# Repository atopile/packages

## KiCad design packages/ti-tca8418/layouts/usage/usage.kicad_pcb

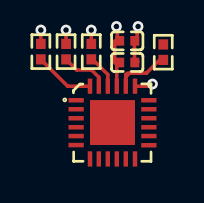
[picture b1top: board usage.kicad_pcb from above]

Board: 2 copper layers, 7 parts (0 on the bottom side), 6 nets.

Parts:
C1: 1±10.0%F; C0402
C2: {7.999..1.2}F; C0402
R1, R2, R3, R4: 10000±1.0%Ω; R0402
U1: WQFN-24_L4.0-W4.0-P0.50-TL-EP2.5

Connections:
SCL: R1.1, U1.23
SDA: R2.1, U1.22
hv: C1.1, C2.1, R1.2, R2.2, R4.2, U1.21
lv: C1.2, C2.2, R3.2, U1.19
nINT: R3.1, U1.24
nRESET: R4.1, U1.20

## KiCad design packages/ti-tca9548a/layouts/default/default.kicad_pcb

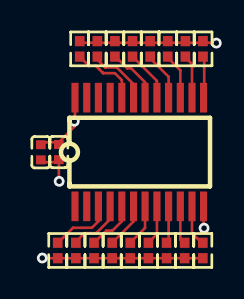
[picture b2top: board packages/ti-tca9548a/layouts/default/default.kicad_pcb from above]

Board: 2 copper layers, 20 parts (0 on the bottom side), 19 nets.

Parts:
C1, C2: [capacitance: unknown]; C0402
R1, R2, R3, R4, R5, R6, R7, R8, R9, R10, R11, R12, R13, R14, R15, R16, R17: [resistance: unknown]; R0402
U1: TSSOP-24_L7.8-W4.4-P0.65-LS6.4-BL

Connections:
hv: C1.1, C2.1, R1.2, R2.2, R3.2, R4.2, R5.2, R6.2, R7.2, R8.2, R9.2, R10.2, R11.2, R12.2, R13.2, R14.2, R15.2, R16.2, R17.2, U1.24
i2cs[0]-SCL: R2.1, U1.5
i2cs[0]-SDA: R10.1, U1.4
i2cs[1]-SCL: R3.1, U1.7
i2cs[1]-SDA: R11.1, U1.6
i2cs[2]-SCL: R4.1, U1.9
i2cs[2]-SDA: R12.1, U1.8
i2cs[3]-SCL: R5.1, U1.11
i2cs[3]-SDA: R13.1, U1.10
i2cs[4]-SCL: R6.1, U1.14
i2cs[4]-SDA: R14.1, U1.13
i2cs[5]-SCL: R7.1, U1.16
i2cs[5]-SDA: R15.1, U1.15
i2cs[6]-SCL: R8.1, U1.18
i2cs[6]-SDA: R16.1, U1.17
i2cs[7]-SCL: R9.1, U1.20
i2cs[7]-SDA: R17.1, U1.19
lv: C1.2, C2.2, U1.1, U1.2, U1.12, U1.21
nRESET: R1.1, U1.3

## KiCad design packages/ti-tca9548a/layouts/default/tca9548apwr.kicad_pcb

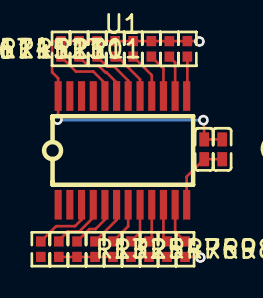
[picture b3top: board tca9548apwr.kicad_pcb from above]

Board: 2 copper layers, 20 parts (0 on the bottom side), 19 nets.

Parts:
C1: 100nF ±10% 16V X7R; C0402
C2: 2.2µF ±20% 6.3V X5R; C0402
R1: 10kΩ ±1% 62.5mW; R0402
R2, R3, R4, R5, R6, R7, R8, R9, R10, R11, R12, R13, R14, R15, R16, R17: 2kΩ ±1% 62.5mW; R0402
U1: TSSOP-24_L7.8-W4.4-P0.65-LS6.4-BL

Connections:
RESET: R1.1, U1.3
SC0: R2.1, U1.5
SC1: R4.1, U1.7
SC2: R6.1, U1.9
SC3: R8.1, U1.11
SC4: R10.1, U1.14
SC5: R12.1, U1.16
SC6: R14.1, U1.18
SC7: R16.1, U1.20
SD0: R3.1, U1.4
SD1: R5.1, U1.6
SD2: R7.1, U1.8
SD3: R9.1, U1.10
SD4: R11.1, U1.13
SD5: R13.1, U1.15
SD6: R15.1, U1.17
SD7: R17.1, U1.19
gnd: C1.2, C2.2, U1.12
hv: C1.1, C2.1, R1.2, R2.2, R3.2, R4.2, R5.2, R6.2, R7.2, R8.2, R9.2, R10.2, R11.2, R12.2, R13.2, R14.2, R15.2, R16.2, R17.2, U1.24

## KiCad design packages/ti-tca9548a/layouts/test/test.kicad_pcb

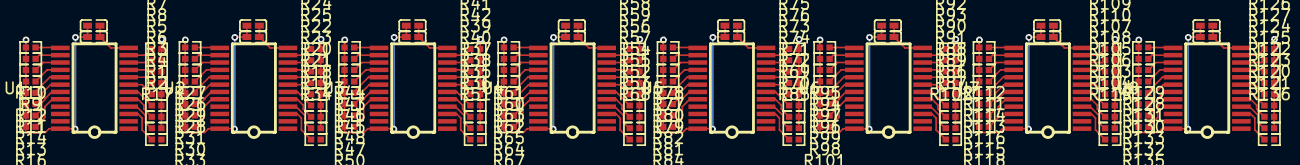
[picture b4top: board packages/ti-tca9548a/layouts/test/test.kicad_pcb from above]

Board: 2 copper layers, 160 parts (0 on the bottom side), 140 nets.

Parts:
C1, C3, C5, C7, C9, C11, C13, C15: 100nF ±10% 16V X7R; C0402
C2, C4, C6, C8, C10, C12, C14, C16: 2.2µF ±20% 6.3V X5R; C0402
R1, R2, R3, R4, R5, R6, R7, R8, R9, R10, R11, R12, R13, R14, R15, R16, R18, R19, R20, R21, R22, R23, R24, R25, R26, R27, R28, R29, R30, R31, R32, R33, R35, R36, R37, R38, R39, R40, R41, R42, R43, R44, R45, R46, R47, R48, R49, R50, R52, R53, R54, R55, R56, R57, R58, R59, R60, R61, R62, R63, R64, R65, R66, R67, R69, R70, R71, R72, R73, R74, R75, R76, R77, R78, R79, R80, R81, R82, R83, R84, R86, R87, R88, R89, R90, R91, R92, R93, R94, R95, R96, R97, R98, R99, R100, R101, R103, R104, R105, R106, R107, R108, R109, R110, R111, R112, R113, R114, R115, R116, R117, R118, R120, R121, R122, R123, R124, R125, R126, R127, R128, R129, R130, R131, R132, R133, R134, R135: 2kΩ ±1% 62.5mW; R0402
R17, R34, R51, R68, R85, R102, R119, R136: 10kΩ ±1% 62.5mW; R0402
U1, U2, U3, U4, U5, U6, U7, U8: TSSOP-24_L7.8-W4.4-P0.65-LS6.4-BL

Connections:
SCL: U1.22, U2.22, U3.22, U4.22, U5.22, U6.22, U7.22, U8.22
SDA: U1.23, U2.23, U3.23, U4.23, U5.23, U6.23, U7.23, U8.23
gnd: C1.2, C2.2, C3.2, C4.2, C5.2, C6.2, C7.2, C8.2, C9.2, C10.2, C11.2, C12.2, C13.2, C14.2, C15.2, C16.2, U1.1, U1.2, U1.12, U1.21, U2.2, U2.12, U2.21, U3.1, U3.12, U3.21, U4.12, U4.21, U5.1, U5.2, U5.12, U6.2, U6.12, U7.1, U7.12, U8.12
hv: C1.1, C2.1, C3.1, C4.1, C5.1, C6.1, C7.1, C8.1, C9.1, C10.1, C11.1, C12.1, C13.1, C14.1, C15.1, C16.1, R1.2, R2.2, R3.2, R4.2, R5.2, R6.2, R7.2, R8.2, R9.2, R10.2, R11.2, R12.2, R13.2, R14.2, R15.2, R16.2, R17.2, R18.2, R19.2, R20.2, R21.2, R22.2, R23.2, R24.2, R25.2, R26.2, R27.2, R28.2, R29.2, R30.2, R31.2, R32.2, R33.2, R34.2, R35.2, R36.2, R37.2, R38.2, R39.2, R40.2, R41.2, R42.2, R43.2, R44.2, R45.2, R46.2, R47.2, R48.2, R49.2, R50.2, R51.2, R52.2, R53.2, R54.2, R55.2, R56.2, R57.2, R58.2, R59.2, R60.2, R61.2, R62.2, R63.2, R64.2, R65.2, R66.2, R67.2, R68.2, R69.2, R70.2, R71.2, R72.2, R73.2, R74.2, R75.2, R76.2, R77.2, R78.2, R79.2, R80.2, R81.2, R82.2, R83.2, R84.2, R85.2, R86.2, R87.2, R88.2, R89.2, R90.2, R91.2, R92.2, R93.2, R94.2, R95.2, R96.2, R97.2, R98.2, R99.2, R100.2, R101.2, R102.2, R103.2, R104.2, R105.2, R106.2, R107.2, R108.2, R109.2, R110.2, R111.2, R112.2, R113.2, R114.2, R115.2, R116.2, R117.2, R118.2, R119.2, R120.2, R121.2, R122.2, R123.2, R124.2, R125.2, R126.2, R127.2, R128.2, R129.2, R130.2, R131.2, R132.2, R133.2, R134.2, R135.2, R136.2, U1.24, U2.1, U2.24, U3.2, U3.24, U4.1, U4.2, U4.24, U5.21, U5.24, U6.1, U6.21, U6.24, U7.2, U7.21, U7.24, U8.1, U8.2, U8.21, U8.24
muxes[0]-RESET: R17.1, U1.3
muxes[0]-SC0: R1.1, U1.5
muxes[0]-SC1: R3.1, U1.7
muxes[0]-SC2: R5.1, U1.9
muxes[0]-SC3: R7.1, U1.11
muxes[0]-SC4: R9.1, U1.14
muxes[0]-SC5: R11.1, U1.16
muxes[0]-SC6: R13.1, U1.18
muxes[0]-SC7: R15.1, U1.20
muxes[0]-SD0: R2.1, U1.4
muxes[0]-SD1: R4.1, U1.6
muxes[0]-SD2: R6.1, U1.8
muxes[0]-SD3: R8.1, U1.10
muxes[0]-SD4: R10.1, U1.13
muxes[0]-SD5: R12.1, U1.15
muxes[0]-SD6: R14.1, U1.17
muxes[0]-SD7: R16.1, U1.19
muxes[1]-RESET: R34.1, U2.3
muxes[1]-SC0: R18.1, U2.5
muxes[1]-SC1: R20.1, U2.7
muxes[1]-SC2: R22.1, U2.9
muxes[1]-SC3: R24.1, U2.11
muxes[1]-SC4: R26.1, U2.14
muxes[1]-SC5: R28.1, U2.16
muxes[1]-SC6: R30.1, U2.18
muxes[1]-SC7: R32.1, U2.20
muxes[1]-SD0: R19.1, U2.4
muxes[1]-SD1: R21.1, U2.6
muxes[1]-SD2: R23.1, U2.8
muxes[1]-SD3: R25.1, U2.10
muxes[1]-SD4: R27.1, U2.13
muxes[1]-SD5: R29.1, U2.15
muxes[1]-SD6: R31.1, U2.17
muxes[1]-SD7: R33.1, U2.19
muxes[2]-RESET: R51.1, U3.3
muxes[2]-SC0: R35.1, U3.5
muxes[2]-SC1: R37.1, U3.7
muxes[2]-SC2: R39.1, U3.9
muxes[2]-SC3: R41.1, U3.11
muxes[2]-SC4: R43.1, U3.14
muxes[2]-SC5: R45.1, U3.16
muxes[2]-SC6: R47.1, U3.18
muxes[2]-SC7: R49.1, U3.20
muxes[2]-SD0: R36.1, U3.4
muxes[2]-SD1: R38.1, U3.6
muxes[2]-SD2: R40.1, U3.8
muxes[2]-SD3: R42.1, U3.10
muxes[2]-SD4: R44.1, U3.13
muxes[2]-SD5: R46.1, U3.15
muxes[2]-SD6: R48.1, U3.17
muxes[2]-SD7: R50.1, U3.19
muxes[3]-RESET: R68.1, U4.3
muxes[3]-SC0: R52.1, U4.5
muxes[3]-SC1: R54.1, U4.7
muxes[3]-SC2: R56.1, U4.9
muxes[3]-SC3: R58.1, U4.11
muxes[3]-SC4: R60.1, U4.14
muxes[3]-SC5: R62.1, U4.16
muxes[3]-SC6: R64.1, U4.18
muxes[3]-SC7: R66.1, U4.20
muxes[3]-SD0: R53.1, U4.4
muxes[3]-SD1: R55.1, U4.6
muxes[3]-SD2: R57.1, U4.8
muxes[3]-SD3: R59.1, U4.10
muxes[3]-SD4: R61.1, U4.13
muxes[3]-SD5: R63.1, U4.15
muxes[3]-SD6: R65.1, U4.17
muxes[3]-SD7: R67.1, U4.19
muxes[4]-RESET: R85.1, U5.3
muxes[4]-SC0: R69.1, U5.5
muxes[4]-SC1: R71.1, U5.7
muxes[4]-SC2: R73.1, U5.9
muxes[4]-SC3: R75.1, U5.11
muxes[4]-SC4: R77.1, U5.14
muxes[4]-SC5: R79.1, U5.16
muxes[4]-SC6: R81.1, U5.18
muxes[4]-SC7: R83.1, U5.20
muxes[4]-SD0: R70.1, U5.4
muxes[4]-SD1: R72.1, U5.6
muxes[4]-SD2: R74.1, U5.8
muxes[4]-SD3: R76.1, U5.10
muxes[4]-SD4: R78.1, U5.13
muxes[4]-SD5: R80.1, U5.15
muxes[4]-SD6: R82.1, U5.17
muxes[4]-SD7: R84.1, U5.19
muxes[5]-RESET: R102.1, U6.3
muxes[5]-SC0: R86.1, U6.5
muxes[5]-SC1: R88.1, U6.7
muxes[5]-SC2: R90.1, U6.9
muxes[5]-SC3: R92.1, U6.11
muxes[5]-SC4: R94.1, U6.14
muxes[5]-SC5: R96.1, U6.16
muxes[5]-SC6: R98.1, U6.18
muxes[5]-SC7: R100.1, U6.20
muxes[5]-SD0: R87.1, U6.4
muxes[5]-SD1: R89.1, U6.6
muxes[5]-SD2: R91.1, U6.8
muxes[5]-SD3: R93.1, U6.10
muxes[5]-SD4: R95.1, U6.13
muxes[5]-SD5: R97.1, U6.15
muxes[5]-SD6: R99.1, U6.17
muxes[5]-SD7: R101.1, U6.19
muxes[6]-RESET: R119.1, U7.3
muxes[6]-SC0: R103.1, U7.5
muxes[6]-SC1: R105.1, U7.7
muxes[6]-SC2: R107.1, U7.9
muxes[6]-SC3: R109.1, U7.11
muxes[6]-SC4: R111.1, U7.14
muxes[6]-SC5: R113.1, U7.16
muxes[6]-SC6: R115.1, U7.18
muxes[6]-SC7: R117.1, U7.20
muxes[6]-SD0: R104.1, U7.4
muxes[6]-SD1: R106.1, U7.6
muxes[6]-SD2: R108.1, U7.8
muxes[6]-SD3: R110.1, U7.10
muxes[6]-SD4: R112.1, U7.13
muxes[6]-SD5: R114.1, U7.15
muxes[6]-SD6: R116.1, U7.17
muxes[6]-SD7: R118.1, U7.19
muxes[7]-RESET: R136.1, U8.3
muxes[7]-SC0: R120.1, U8.5
muxes[7]-SC1: R122.1, U8.7
muxes[7]-SC2: R124.1, U8.9
muxes[7]-SC3: R126.1, U8.11
muxes[7]-SC4: R128.1, U8.14
muxes[7]-SC5: R130.1, U8.16
muxes[7]-SC6: R132.1, U8.18
muxes[7]-SC7: R134.1, U8.20
muxes[7]-SD0: R121.1, U8.4
muxes[7]-SD1: R123.1, U8.6
muxes[7]-SD2: R125.1, U8.8
muxes[7]-SD3: R127.1, U8.10
muxes[7]-SD4: R129.1, U8.13
muxes[7]-SD5: R131.1, U8.15
muxes[7]-SD6: R133.1, U8.17
muxes[7]-SD7: R135.1, U8.19

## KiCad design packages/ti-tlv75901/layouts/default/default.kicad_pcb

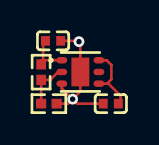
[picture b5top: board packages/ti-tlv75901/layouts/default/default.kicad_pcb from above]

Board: 2 copper layers, 5 parts (0 on the bottom side), 5 nets.

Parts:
C1, C2: 1µF ±10%; C0402
R1: 23.2kΩ ±1%; R0402
R2: 28.7kΩ ±1%; R0402
U1: WSON-6_L2.0-W2.0-P0.65-TL-EP

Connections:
hv: C1.1, U1.4, U1.6
lv: C1.2, U1.3
output_decoupling_capacitor-power-hv: C2.1, R1.1, U1.1
output_decoupling_capacitor-power-lv: C2.2, R2.2, U1.7
ref_out-hv: R1.2, R2.1, U1.2

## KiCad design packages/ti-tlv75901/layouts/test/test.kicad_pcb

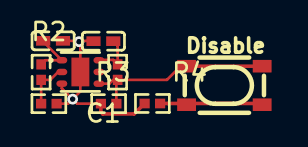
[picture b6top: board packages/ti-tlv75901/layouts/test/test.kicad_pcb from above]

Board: 2 copper layers, 9 parts (0 on the bottom side), 6 nets.

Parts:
C1, C2: 1µF ±10% 25V X5R; C0402
R1: 47kΩ ±1% 62.5mW; R0402
R2: 2kΩ ±1% 62.5mW; R0402
R3: 10kΩ ±1% 62.5mW; R0402
R4: 120kΩ ±1% 62.5mW; R0402
R5: 1kΩ ±1% 62.5mW; R0402
SW1: KEY-SMD_4P-L4.2-W3.2-P2.20-LS4.6
U1: WSON-6_L2.0-W2.0-P0.65-TL-EP

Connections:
-hv-0: C1.1, R4.1, U1.6
-hv-1: C2.1, R3.1, U1.1
FB: R2.1, R3.2, U1.2
gnd: C1.2, C2.2, R1.2, R2.2, R5.2, U1.3, U1.7
input: R5.1, SW1.1, SW1.2
output: R1.1, R4.2, SW1.3, SW1.4, U1.4
